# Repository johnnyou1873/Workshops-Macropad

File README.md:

# Workshops-Macropad
A custom 6-key keyboard with rotary encoder, 3D-printed case with integrated plate mounting, and VIA firmware.

## Bill of Materials
### Required
 - 1x Seeed Studio XIAO RP2040
 - 6x MX hotswap sockets
 - 7x 1N4148 small signal diodes
 - 1x EC11 rotary encoder with push button
 - 4x M3x12 screws (support M3x8 - M3x14) (or the 3D printable pegs/rivets)

### Optional for RGB
 - 6x SK-6812 MINI-E reverse-mount RGB LEDs
 - 6x 100n 0805 decoupling capacitors
 - 2x 10k 0805 pull-up resistors
 - 1x BSS138 N-channel MOSFET

### Optional for GPIO
 - 4x 2.54mm pitch male right-angle pin headers

## Assembly Instructions (Basic)

1. 3D print the top case, bottom case, and knob. If not using screws, print the pegs/rivets. For the best results, print the top case and bottom case with 100% infill.
2. Solder the hotswap sockets and diodes, taking note of the polarity. These components belong on the side with the "mini macropad" text.
3. Solder the microcontroller, using pin headers to align the pads but not soldering the pin headers.
4. Solder the rotary encoder on the opposite side of the board as the rest of the components.
5. Press and hold the BOOT button on the microcontroller. Then, while still holding the button, plug in the microcontroller to a computer. The microcontroller should appear as a virtual USB storage device.
6. Upload the .uf2 firmware file to the microcontroller. The virtual USB storage device should disconnect once flashed.
7. Unplug and replug the USB cable.
8. Test that the keys work by inserting switches into the hotswap sockets and depressing them. The keys should type the numbers 1-6 by default.
9. Test that the rotary encoder works by rotating it and pressing it. The encoder should control volume when rotated and type the number 7 when pressed.
10. Unplug the USB cable.
11. Insert the completed PCB into the bottom case, slotting in the USB conector first.
12. Place the top case on top of the bottom case.
13. Secure the bottom case to the top case with the M3x12 screws or the printable pegs/rivets.
14. Insert the switches into the top case. The switches should securely slot into the hotswap sockets.
15. Attach the keycaps and knob to the key switches and rotary encoder.
16. Connect the USB cable.
17. Open the [VIA app](https://www.usevia.app/).
18. Go to the "Settings" tab and enable "Show Design tab".
19. Go to the "Design" tab and upload the .json file.
20. Go to the "Configure" tab. After authorizing the device, the macropad is now configurable!

### Notes

On MacOS, plugging in the macropad for the first time after programming may trigger a message about keyboard layout. Because the macropad has a nonstandard layout, this message can be ignored. The keyboard should work with the configuration set with VIA.

RGB is implemented on the PCB but has not been tested.

To leverage the GPIO pins fully, custom firmware is needed.

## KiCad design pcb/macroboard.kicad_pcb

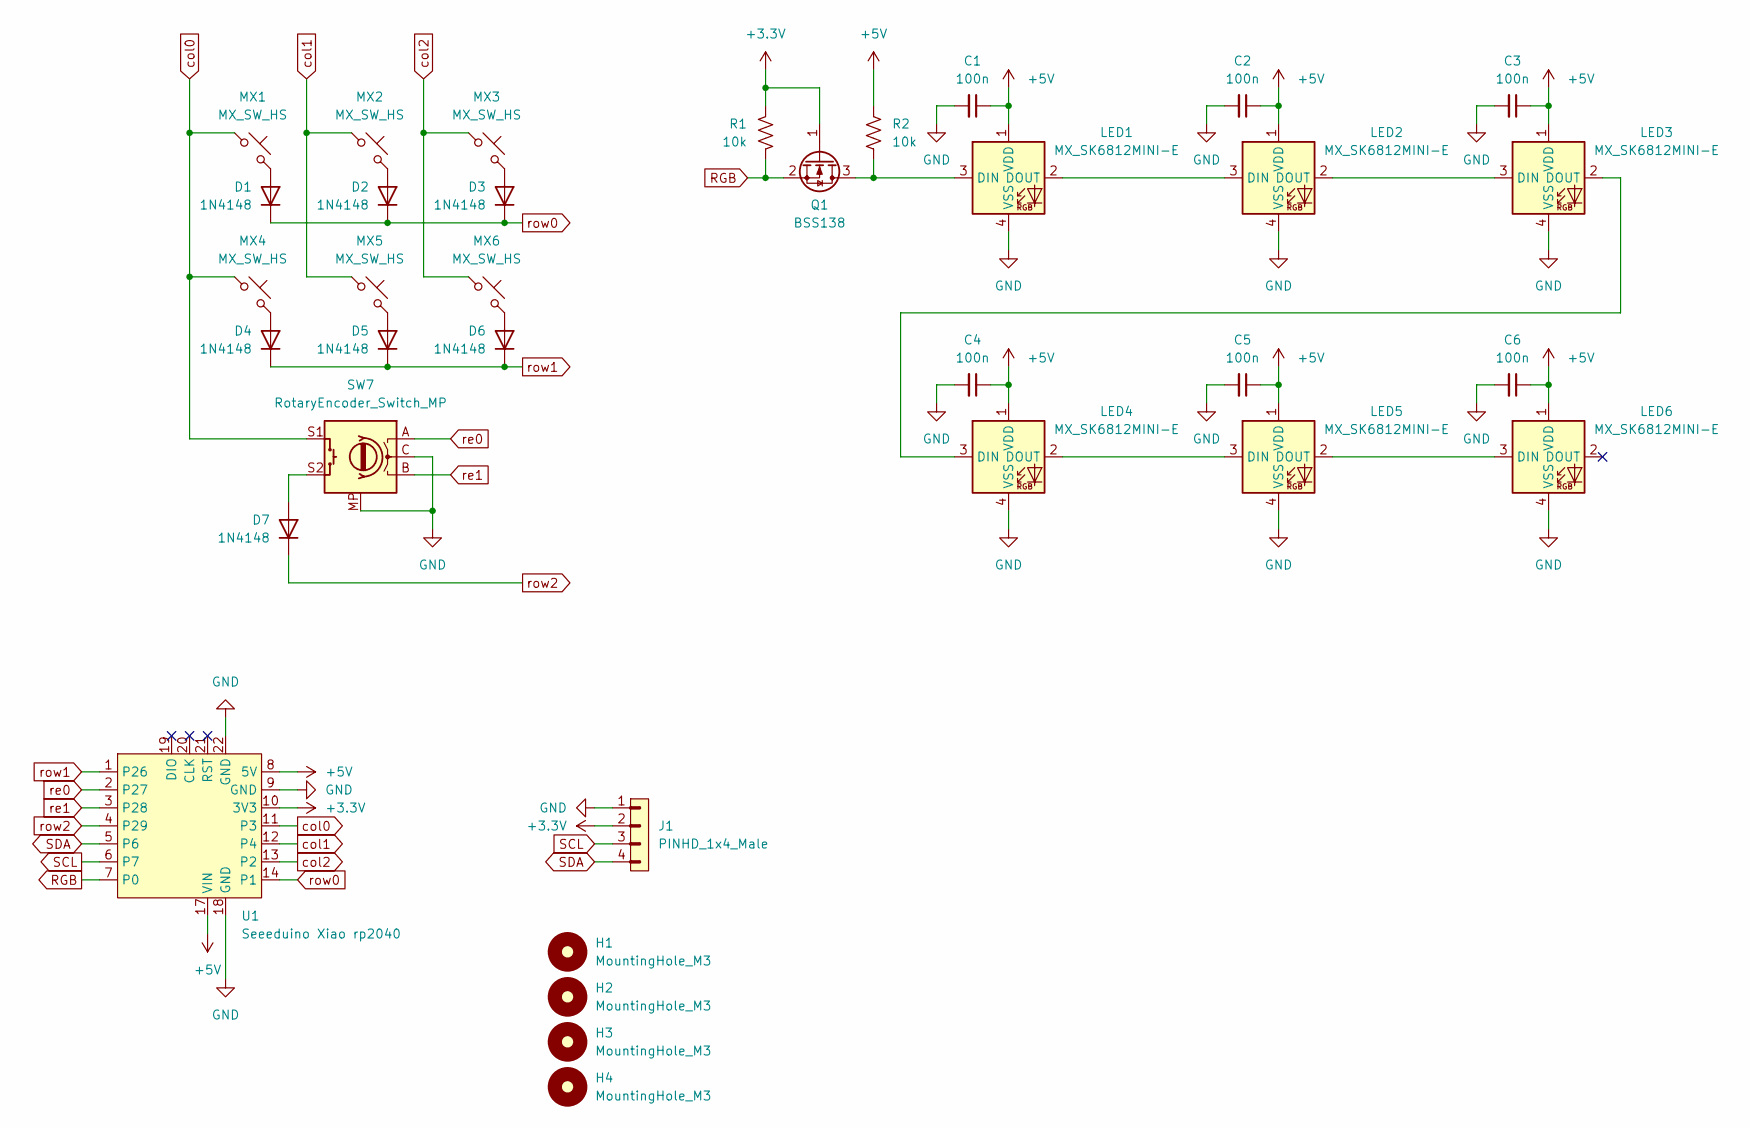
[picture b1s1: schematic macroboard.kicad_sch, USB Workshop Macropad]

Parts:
C1, C2, C3, C4, C5, C6: 100n; C_0805_2012Metric_Pad1.18x1.45mm_HandSolder
D1, D2, D3, D4, D5, D6, D7: 1N4148; D_DO-35_SOD27_P7.62mm_Horizontal_Hybrid
H1, H2, H3, H4: MountingHole_M3; MountingHole_3.2mm_M3_Pad
J1: PINHD_1x4_Male; PinHeader_1x04_P2.54mm_Horizontal
LED1, LED2, LED3, LED4, LED5, LED6: MX_SK6812MINI-E; LED_MX_6028R
MX1, MX2, MX3, MX4, MX5, MX6: MX_SW_HS; SW_MX_HS_CPG151101S11_1u
Q1: BSS138; SOT-23
R1, R2: 10k; R_0805_2012Metric_Pad1.20x1.40mm_HandSolder
SW7: RotaryEncoder_Switch_MP; ROT_Alps_EC11E-Switch
U1: Seeeduino Xiao rp2040; Xiao_rp2040_ACH

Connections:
+3.3V: J1.2, Q1.1 (G), R1.2, U1.10 (3V3)
+5V: C1.1, C2.1, C3.1, C4.1, C5.1, C6.1, LED1.1 (VDD), LED2.1 (VDD), LED3.1 (VDD), LED4.1 (VDD), LED5.1 (VDD), LED6.1 (VDD), R2.2, U1.8 (5V), U1.17 (VIN)
GND: C1.2, C2.2, C3.2, C4.2, C5.2, C6.2, J1.1, LED1.4 (VSS), LED2.4 (VSS), LED3.4 (VSS), LED4.4 (VSS), LED5.4 (VSS), LED6.4 (VSS), SW7.C, SW7.MP, U1.9 (GND), U1.18 (GND), U1.22 (GND)
unnamed: D1.2 (A), MX1.2
unnamed: D2.2 (A), MX2.2
unnamed: D3.2 (A), MX3.2
unnamed: D4.2 (A), MX4.2
unnamed: D5.2 (A), MX5.2
unnamed: D6.2 (A), MX6.2
unnamed: D7.2 (A), SW7.S2
unnamed: LED1.3 (DIN), Q1.3 (D), R2.1
unnamed: LED1.2 (DOUT), LED2.3 (DIN)
unnamed: LED2.2 (DOUT), LED3.3 (DIN)
unnamed: LED3.2 (DOUT), LED4.3 (DIN)
unnamed: LED4.2 (DOUT), LED5.3 (DIN)
unnamed: LED5.2 (DOUT), LED6.3 (DIN)
RGB: Q1.2 (S), R1.1, U1.7 (P0)
SCL: J1.3, U1.6 (P7)
SDA: J1.4, U1.5 (P6)
col0: MX1.1, MX4.1, SW7.S1, U1.11 (P3)
col1: MX2.1, MX5.1, U1.12 (P4)
col2: MX3.1, MX6.1, U1.13 (P2)
re0: SW7.A, U1.2 (P27)
re1: SW7.B, U1.3 (P28)
row0: D1.1 (K), D2.1 (K), D3.1 (K), U1.14 (P1)
row1: D4.1 (K), D5.1 (K), D6.1 (K), U1.1 (P26)
row2: D7.1 (K), U1.4 (P29)

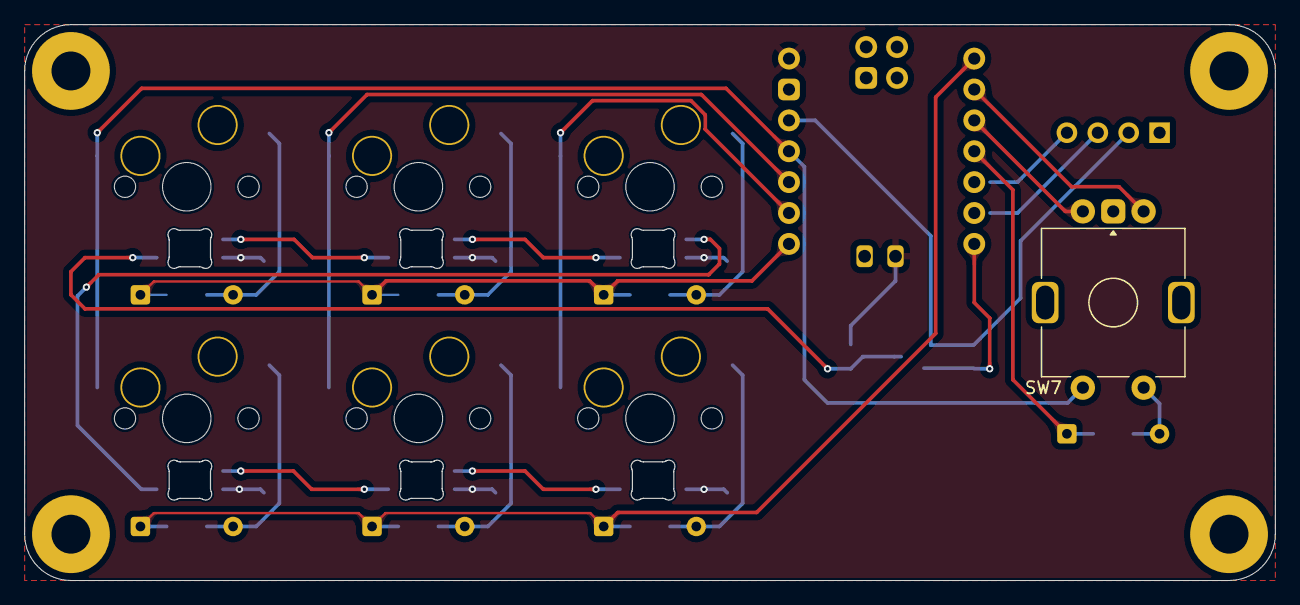
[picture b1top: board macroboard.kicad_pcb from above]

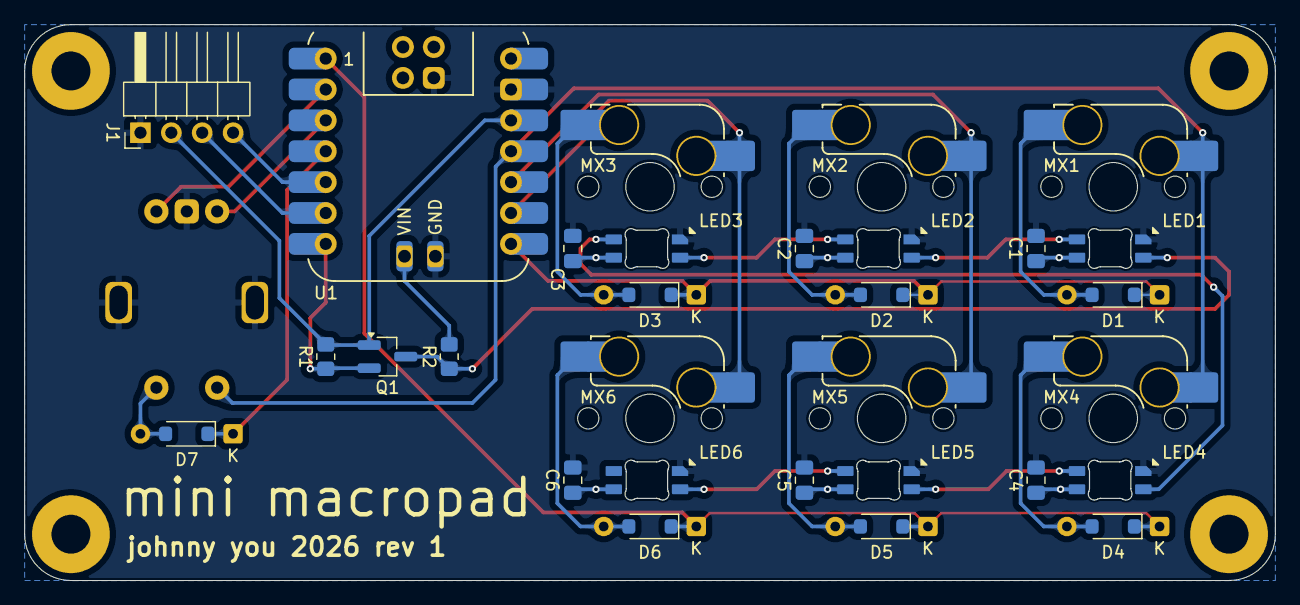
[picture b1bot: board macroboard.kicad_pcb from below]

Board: 2 copper layers, 102.9 x 45.7 mm, 35 parts (30 on the bottom side), 27 nets.

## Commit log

2026-05-05 Update README with RGB notes and bill of materials
    Added notes on RGB implementation and a detailed bill of materials.
2026-05-05 Added QMK source files and organized CAD files.
2026-05-08 Update VIA JSON to fully support rotary encoder.
2026-05-11 Clean up 3D files
2026-05-15 Add printable peg to sub M3 screw
2026-05-16 Update README with assembly instructions and BOM details
    Added assembly instructions and additional details to the Bill of Materials.
2026-05-16 Update README to clarify notes and remove redundancy
    Removed redundant note about RGB implementation and custom firmware from the README. Added clarification under a new 'Notes' section.
